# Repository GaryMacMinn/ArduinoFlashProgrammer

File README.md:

# ArduinoFlashProgrammer
In designing my 65C02 retro computer I realised I'd be needing to program some Flash
memory chips to be the ROMs of my system. My old parallel EPROM programmer is long gone
so a new design was called for.

I had an Arduino Mega 2560 on the bench when the light dawned that this would be a good
platform to do this as it had plenty of I/O lines to operate the 27 address and data lines
and was fairly easy to program.

And so was born, the Arduino Flash Programmer.

The code shown here supports the AMD AM29F040B specifically as this is the Flash chip I'm
using. These are available on eBay and the like at cheap prices. They are a 4Mbit chip
arranged as 512k x 8bit. The sector operations work on 64k sectors so there are only 8 sectors
in this chip.

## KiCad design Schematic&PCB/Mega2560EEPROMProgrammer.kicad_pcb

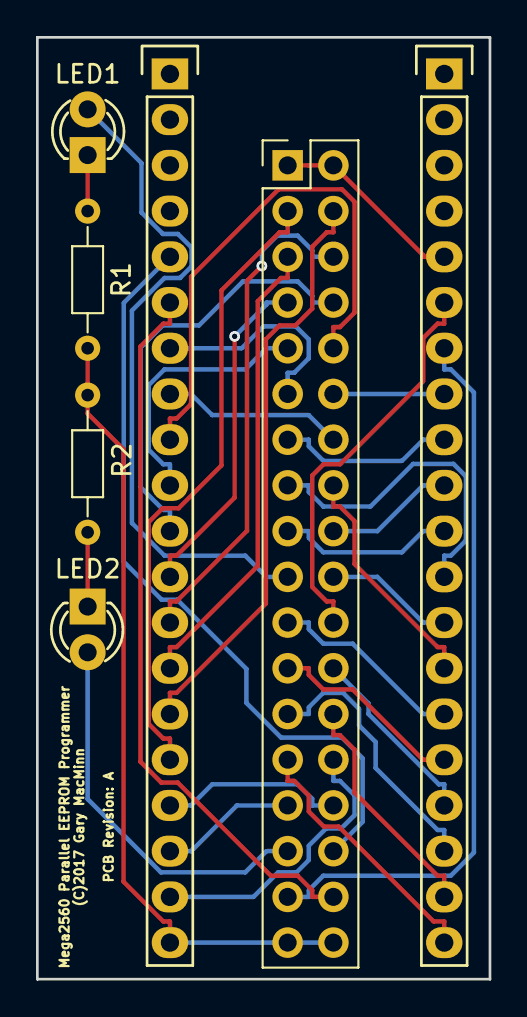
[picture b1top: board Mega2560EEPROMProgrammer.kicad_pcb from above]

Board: 2 copper layers, 25.1 x 52.3 mm, 7 parts (0 on the bottom side), 36 nets.

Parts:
LED1: Red; LED-3MM
LED2: Green; LED-3MM
P1: Mega2560 I/O; Pin_Header_Straight_2x18_Pitch2.54mm
P21, P22: CONN_01X20; Socket_Strip_Straight_1x20
R1, R2: 220R; R_Axial_DIN0204_L3.6mm_D1.6mm_P7.62mm_Horizontal

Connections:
+5v: P1.1, P1.2, P22.5
-CE: P1.21, P22.15
-OE: P1.20, P22.13
-WE: P1.22, P22.6
A0: P1.3, P21.16
A1: P1.4, P21.15
A2: P1.5, P21.14
A3: P1.6, P21.13
A4: P1.7, P21.12
A5: P1.8, P21.11
A6: P1.9, P21.10
A7: P1.10, P21.9
A8: P1.18, P22.10
A9: P1.17, P22.11
A10: P1.16, P22.14
A11: P1.15, P22.12
A12: P1.14, P21.8
A13: P1.13, P22.9
A14: P1.12, P22.8
A15: P1.11, P21.7
A16: P1.34, P21.6
A17: P1.33, P22.7
A18: P1.32, P21.5
D0: P1.30, P21.17
D1: P1.29, P21.18
D2: P1.28, P21.19
D3: P1.27, P22.20
D4: P1.26, P22.19
D5: P1.25, P22.18
D6: P1.24, P22.17
D7: P1.23, P22.16
GND: P1.35, P1.36, P21.20, R1.2, R2.2
unnamed: LED1.1, R1.1
unnamed: LED1.2, P1.19
unnamed: LED2.1, R2.1
unnamed: LED2.2, P1.31

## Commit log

2017-09-22 Create LICENSE
2017-09-23 Initial setup and uploads
    Addes source and circuit files.
2017-10-03 Fixed sector erase and implement full device erase.
2017-10-03 File name update
2017-10-03 File update

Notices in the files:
Schematic&PCB/Mega2560EEPROMProgrammer.kicad_pcb:
(C)2017 Gary MacMinn
